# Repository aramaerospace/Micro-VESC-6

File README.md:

# Micro-VESC-6
Micro VESC-6:  44mmx34mm PCB packs the VESC 6 with 6xPowerTDFN FETS. 3.3V regulator only.
Update: I have been working with VESC for the last few years and would love to revisit the Micro-VESC-6 design. The one which is published currently can be improved a lot, to say the least. 
I plan to publish much better version within the next 3-5 months. Thanks!

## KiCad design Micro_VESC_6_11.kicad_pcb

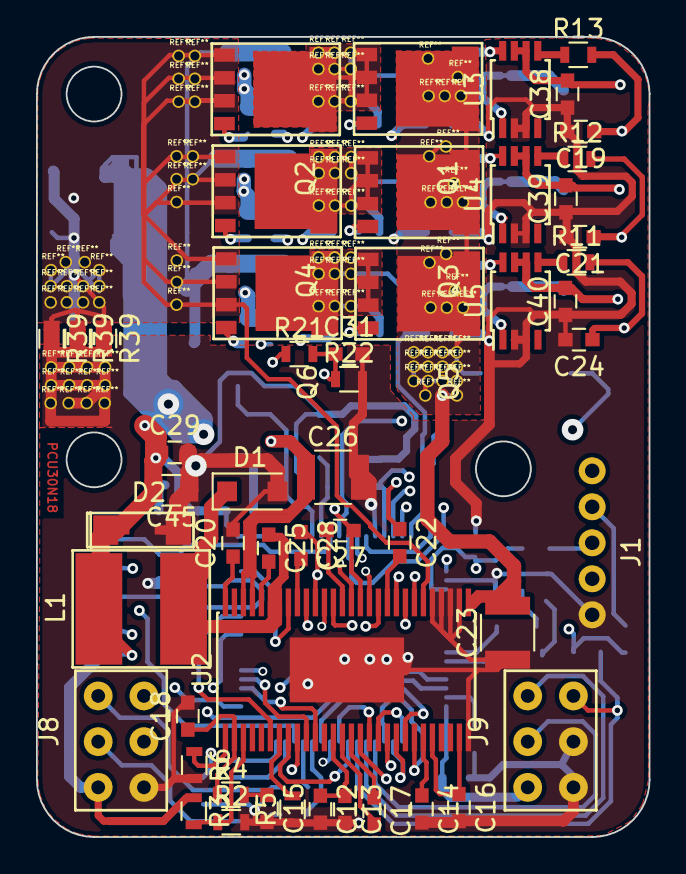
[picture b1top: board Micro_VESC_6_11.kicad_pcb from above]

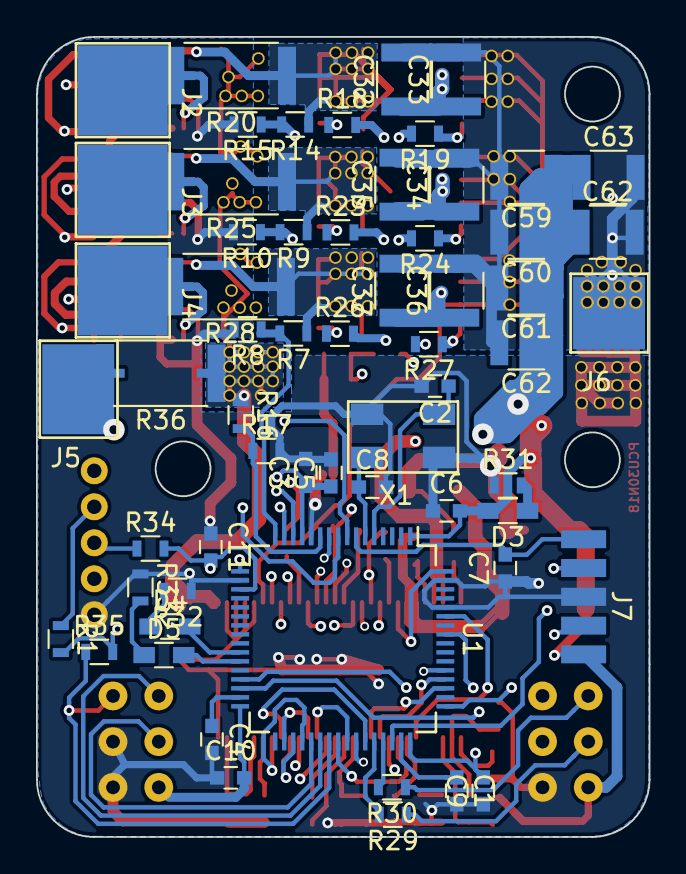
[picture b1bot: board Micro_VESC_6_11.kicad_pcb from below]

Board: 4 copper layers, 34.0 x 44.5 mm, 112 parts (60 on the bottom side), 82 nets.

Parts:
C1, C3, C4, C5, C6, C9, C10, C11, C12, C13, C14, C16, C29, C38, C39, C40: 2.2u; C_0603
C2, C8: 15p; C_0603
C7, C25: 100n; C_0603
C15: 750p; C_0603
C17: 22n; C_0603
C18: 6.8p; C_0603
C19, C21, C24: 4.7n; C_0603
C20: 6.8n; C_0603
C22, C27, C28: 220n; C_0603
C23, C26, C32, C33, C34, C35, C36, C37: 4.7u_100V; C_1210
C31: 2u2; C_0603
C45: 22u_16V; C_0805
C59, C60, C61, C62, C62#2, C63: 10u_50V; C_1210
D1: B260S1F-7; D_SOD-123F
D2: TVS 5V; DO-214AC_SOD-323
D3: BLUE; R_0603_HandSoldering
D4: GREEN; R_0603_HandSoldering
D5: RED; R_0603_HandSoldering
J1: Motor_Conn; Wire_Pad_Thru_1x5
J2, J3, J4, J5, J6: CONN_01X01; PAD_5x5mm
J7: SWD; SWD_5PIN
J8: COMM_1; 2x6_2_54MezConn
J9: COMM_2; 2x6_2_54MezConn
L1: 47u; Inductor_SRR6038-220Y
Q1: NTMFS5C604NLT1G; SO8FL_UNIVERSAL
Q2, Q3, Q4, Q5, Q6: Q_NMOS_GSD; SO8FL_UNIVERSAL
R1, R8, R10, R15, R17, R34, R35: 2k2; R_0603
R2, R5, R22: 10k; R_0603
R3: 32.4k; R_0603
R4: 147k; R_0603
R6: 732k; R_0603
R7, R9, R14, R16: 39k; R_0603
R11, R12, R13: 100R; R_0603
R18, R19, R23, R24, R26, R27: 4.7R; R_0603
R20, R25, R28, R36: 0.0005R; R_2512_SHUNT
R21: NTC 10k; R_0603
R29, R30: 22R; R_0603
R31: 1k; R_0603
R32, R33: 220R; R_0603
R39, R39#2, R39#3: 0R; R_0603
U1: STM32F40X_LQFP64; LQFP-64_10x10mm_Pitch0.5mm
U2: DRV8301; HTSSOP-56-1EP_6.1x14mm_Pitch0.5mm
U3, U4, U5: AD8418; TSSOP-8_3x3mm_Pitch0.65mm
X1: 8m; CRYSTAL_ABM3B

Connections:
/CS: U1.40, U2.8
/CURR_A: C19.1, R13.2, U1.8
/CURR_B: C21.1, R12.2, U1.9
/CURR_C: C24.1, R11.2, U1.10
/EN_GATE: U1.57, U2.16
/FAULT: U1.59, U2.6
/HALL_1: J1.2, J9.2, R1.1, U1.37
/HALL_2: J1.3, J9.3, R34.1, U1.38
/HALL_3: J1.4, J9.4, R35.1, U1.39
/INH_A: U1.41, U2.17
/INH_B: U1.42, U2.19
/INH_C: U1.43, U2.21
/INL_A: U1.34, U2.18
/INL_B: U1.35, U2.20
/INL_C: U1.36, U2.22
/LED_GREEN: D4.2, U1.26
/LED_RED: D5.2, U1.27
/NRST: C7.2, J7.1, U1.7
/RX_SDA_NSS: J8.5, U1.30
/SCKL: U1.51, U2.11
/SDI: U1.53, U2.9
/SDO: U1.52, U2.10
/SENS_A: R14.2, R15.1, U1.14
/SENS_B: R9.2, R10.1, U1.15
/SENS_C: R7.2, R8.1, U1.16
/SENS_SUPPLY: R16.2, R17.1, U1.11
/SUPPLY: C23.2, C26.1, C32.1, C33.1, C34.1, C35.1, C36.1, C37.1, C59.1, C60.1, C61.1, C62.1, C62#2.1, C63.1, J5.1, Q1.3, Q3.3, Q5.3, R16.1, R36.1, R36.2, R36.3, R36.4, U2.29, U2.53, U2.54
/SWCLK: J7.4, U1.49
/SWDIO: J7.2, U1.46
/TEMP: C31.1, R21.2, R22.1, U1.17
/TX_SCL_MOSI: J8.4, U1.29
/USB_DM: J8.2, R29.1
/USB_DP: J8.3, R30.1
GND: C1.2, C2.2, C3.2, C4.2, C5.2, C6.1, C7.1, C8.2, C9.1, C10.1, C11.1, C12.2, C13.2, C14.2, C15.2, C16.2, C18.2, C19.2, C20.2, C21.2, C23.1, C24.2, C26.2, C29.2, C31.2, C38.1, C39.1, C40.1, C45.1, D1.2, D2.2, J1.5, J7.3, J8.6, J9.5, J9.6, R2.2, R5.1, R6.2, R8.2, R10.2, R15.2, R17.2, R22.2, R31.1, R32.1, R33.1, R39.2, R39#2.2, R39#3.2, U1.12, U1.18, U1.60, U1.63, U2.28, U2.30, U2.31, U2.32, U2.33, U2.57, U3.2, U3.3, U4.2, U4.3, U5.2, U5.3, X1.2, X1.4
GNDPWR: C32.2, C33.2, C34.2, C35.2, C36.2, C37.2, C59.2, C60.2, C61.2, C62.2, C62#2.2, C63.2, J6.1, Q2.2, Q4.2, Q6.2, R39.1, R39#2.1, R39#3.1, U2.34, U2.39, U2.44
unnamed: C1.1, U1.47
unnamed: C2.1, U1.5, X1.1
unnamed: C4.1, U1.31
unnamed: C8.1, U1.6, X1.3
unnamed: C12.1, C13.1, U2.13
unnamed: C14.1, U2.23
unnamed: C15.1, R4.2
unnamed: C16.1, U2.24, U2.27
unnamed: C17.1, U2.15
unnamed: C17.2, U2.14
unnamed: C18.1, R4.1, U2.2
unnamed: C20.1, U2.56
unnamed: C22.1, Q5.2, Q6.3, R7.1, R28.1, R28.3, U2.36, U5.8
unnamed: C22.2, U2.38
unnamed: C25.1, D1.1, L1.2, U2.50, U2.51
unnamed: C25.2, U2.52
unnamed: C27.1, Q3.2, Q4.3, R9.1, R25.1, R25.3, U2.41, U4.8
unnamed: C27.2, U2.43
unnamed: C28.1, Q1.2, Q2.3, R14.1, R20.1, R20.3, U2.46, U3.8
unnamed: C28.2, U2.48
unnamed: D3.1, R31.2
unnamed: D4.1, R32.2
unnamed: D5.1, R33.2
unnamed: J2.1, R20.2, R20.4, U3.1
unnamed: J3.1, R25.2, R25.4, U4.1
unnamed: J4.1, R28.2, R28.4, U5.1
unnamed: Q1.1, R18.1
unnamed: Q2.1, R19.1
unnamed: Q3.1, R23.1
unnamed: Q4.1, R24.1
unnamed: Q5.1, R26.1
unnamed: Q6.1, R27.1
unnamed: R2.1, R3.2, U2.3
unnamed: R5.2, U2.7
unnamed: R6.1, U2.1
unnamed: R11.1, U5.5
unnamed: R12.1, U4.5
unnamed: R13.1, U3.5
unnamed: R18.2, U2.47
unnamed: R19.2, U2.45
unnamed: R23.2, U2.42
unnamed: R24.2, U2.40
unnamed: R26.2, U2.37
unnamed: R27.2, U2.35
unnamed: R29.2, U1.44
unnamed: R30.2, U1.45
VCC: C3.1, C5.1, C6.2, C9.2, C10.2, C11.2, C29.1, C38.2, C39.2, C40.2, C45.2, D2.1, D3.2, J1.1, J7.5, J8.1, J9.1, L1.1, R1.2, R3.1, R21.1, R34.2, R35.2, U1.1, U1.13, U1.19, U1.32, U1.48, U1.64, U2.49, U3.6, U3.7, U4.6, U4.7, U5.6, U5.7

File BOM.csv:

R31,1k,ESR03EZPJ102
"R32,33",220R,ESR03EZPJ221
Q1-Q6,,NTMFS5C604NLT1G
"R1,R34,R35,R8,R10,R15,R17",2k2,RC0603FR-072K2L
D3,LED BLE,LB Q39G-L2OO-35-1
D4,GREEN,LTST-C191KGKT
D5,RED,LTST-C191KRKT
"R29,R30",22R,ERJ-3EKF22R0V
"J8,J8*(on PCB only)","COMM1,COMM2",68683-303LF
"C2,C8",15pF,GRM1885C2A150JA01D
"C7,C25",0.1uF,06035G104ZAT2A
"C1,C3,C4,C5,C6,C9,C10,C11,C12,C13,C14,C16,C29,C31,C38,C39,C40",2.2uF,GRM188R6YA225MA12D
X1,,ABM3B-8.000MHZ-10-1-U-T
"R2,R5,R22",10k,RR1220P-103-D
R3,32.4k,ERJ-3EKF3242V
R4,147k,ERJ-3EKF1473V
R6,732k,CRCW0603732KFKEA
C15,750p,CL10B751KB8NNNC
C18,6.8p,CGA3E2NP02A6R8D080AA
C17,0.022uF,CL10B223KB8NNWC
C20,6.8nF,06035C682J4T2A
"C22,C27,C28",220nF,GCM188R71H224KA64D
"R7,R9,R14,R16",39k,AC0603FR-0739KL
R21,NTC 10k,B57330V2103F260
"R18,R19,R23,R24,R26,R27",4R7,RK73B1JTTD4R7J
"C19,C21,C24",4.7nF,CL10B472KC8NNNC
"R11,R12,R13",100R,RC0603FR-07100RL
"R20,R25,R28,R36(on PCB only)",.005R,WSLF2512L5000FEA
"U3,U4,U5",,AD8418WBRMZ
U1,,STM32F405RGT6
U2,,DRV8301DCAR
"C23,C26,C32,C33,C34,C35,C36,C37",4.7uF,C1206C475K5PACTU
"C59,C60,C61,C62,C63",10uF,UMK316BBJ106ML-T
C45,22uF,CL21A226MOCLRNC
L1,47uH,TYS5040470M-10
D1,,SMD26PL-TP

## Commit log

2019-09-02 Add files via upload
    Updated the kicad_pcb file: corrected some track placements.
